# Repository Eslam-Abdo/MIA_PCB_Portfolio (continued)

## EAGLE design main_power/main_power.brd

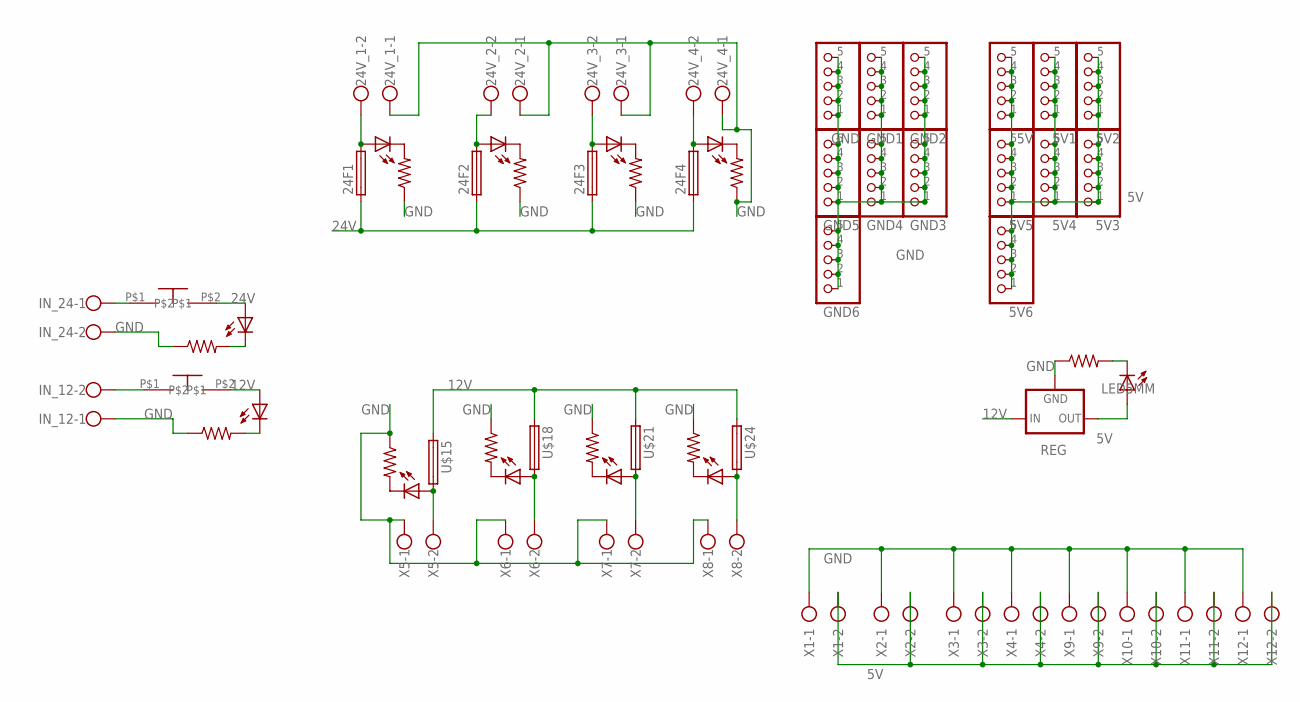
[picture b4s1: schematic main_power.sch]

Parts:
5V, 5V1, 5V2, 5V3, 5V4, 5V5, 5V6: PINHD-1X5; 1X05
12IN: RES-7; 0204/7
12IND: LED5MM
24F1, 24F2, 24F3, 24F4: FUSE_HOLDER; SH22,5A
24V_1, 24V_2, 24V_3, 24V_4: ROSTA.POWER; W239-302
GND, GND1, GND2, GND3, GND4, GND5, GND6: PINHD-1X5; 1X05
IN24: LED5MM
INR24: RES-7; 0204/7
IN_12, IN_24: ROSTA.POWER; W239-302
REG: 78XX-METAL; TO3-79
U$1: 2k; 0204/7
U$2: LED5MM
U$4, U$7, U$10, U$13, U$16, U$19, U$22, U$25: LED3MM
U$5, U$8, U$11, U$14, U$17, U$20, U$23, U$26: RES-7; 0204/7
U$15, U$18, U$21, U$24: FUSE_HOLDER; SH22,5A
U$27, U$28: SWITCH_2; ON_OFF
X1, X2, X3, X4, X9, X10, X11, X12: AK300/22; XTALRR488W60L1090T465H350B
X5, X6, X7, X8: ROSTA.POWER; W239-302

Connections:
5V: 5V.1, 5V.2, 5V.3, 5V.4, 5V.5, 5V1.1, 5V1.2, 5V1.3, 5V1.4, 5V1.5, 5V2.1, 5V2.2, 5V2.3, 5V2.4, 5V2.5, 5V3.1, 5V3.2, 5V3.3, 5V3.4, 5V3.5, 5V4.1, 5V4.2, 5V4.3, 5V4.4, 5V4.5, 5V5.1, 5V5.2, 5V5.3, 5V5.4, 5V5.5, 5V6.1, 5V6.2, 5V6.3, 5V6.4, 5V6.5, REG.1 (OUT), U$2.A, X1.2, X2.2, X3.2, X4.2, X9.2, X10.2, X11.2, X12.2
12V: 12IND.A, REG.3 (IN), U$15.1, U$18.1, U$21.1, U$24.1, U$28.P$2
24V: 24F1.1, 24F2.1, 24F3.1, 24F4.1, IN24.A, U$27.P$2
GND: 12IN.1, 24V_1.1, 24V_2.1, 24V_3.1, 24V_4.1, GND.1, GND.2, GND.3, GND.4, GND.5, GND1.1, GND1.2, GND1.3, GND1.4, GND1.5, GND2.1, GND2.2, GND2.3, GND2.4, GND2.5, GND3.1, GND3.2, GND3.3, GND3.4, GND3.5, GND4.1, GND4.2, GND4.3, GND4.4, GND4.5, GND5.1, GND5.2, GND5.3, GND5.4, GND5.5, GND6.1, GND6.2, GND6.3, GND6.4, GND6.5, INR24.1, IN_12.1, IN_24.2, REG.2 (GND), U$1.1, U$5.1, U$8.1, U$11.1, U$14.1, U$17.1, U$20.1, U$23.1, U$26.1, X1.1, X2.1, X3.1, X4.1, X5.1, X6.1, X7.1, X8.1, X9.1, X10.1, X11.1, X12.1
unnamed: U$1.2, U$2.K (C)
unnamed: 24F1.2, 24V_1.2, U$4.A
unnamed: U$4.K (C), U$5.2
unnamed: IN_12.2, U$28.P$1
unnamed: 24F2.2, 24V_2.2, U$7.A
unnamed: U$7.K (C), U$8.2
unnamed: IN_24.1, U$27.P$1
unnamed: 24F3.2, 24V_3.2, U$10.A
unnamed: U$10.K (C), U$11.2
unnamed: IN24.K (C), INR24.2
unnamed: 24F4.2, 24V_4.2, U$13.A
unnamed: U$13.K (C), U$14.2
unnamed: 12IN.2, 12IND.K (C)
unnamed: U$15.2, U$16.A, X5.2
unnamed: U$16.K (C), U$17.2
unnamed: U$18.2, U$19.A, X6.2
unnamed: U$19.K (C), U$20.2
unnamed: U$21.2, U$22.A, X7.2
unnamed: U$22.K (C), U$23.2
unnamed: U$24.2, U$25.A, X8.2
unnamed: U$25.K (C), U$26.2

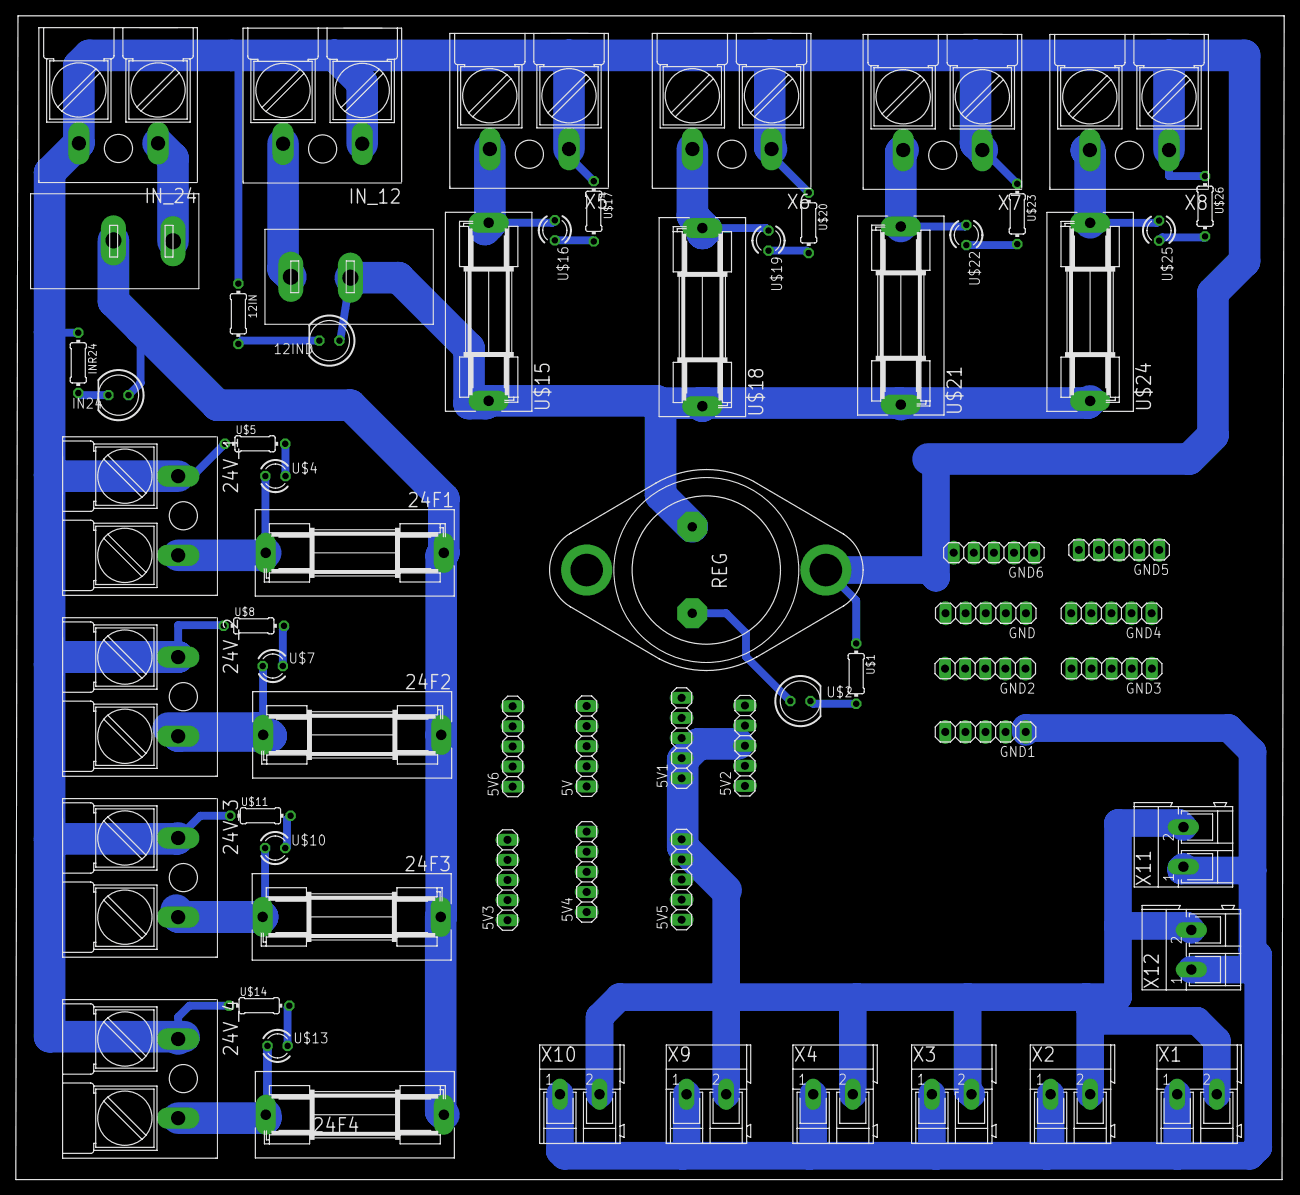
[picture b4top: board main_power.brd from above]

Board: 2 copper layers, 160.3 x 147.1 mm, 65 parts (0 on the bottom side), 25 nets.

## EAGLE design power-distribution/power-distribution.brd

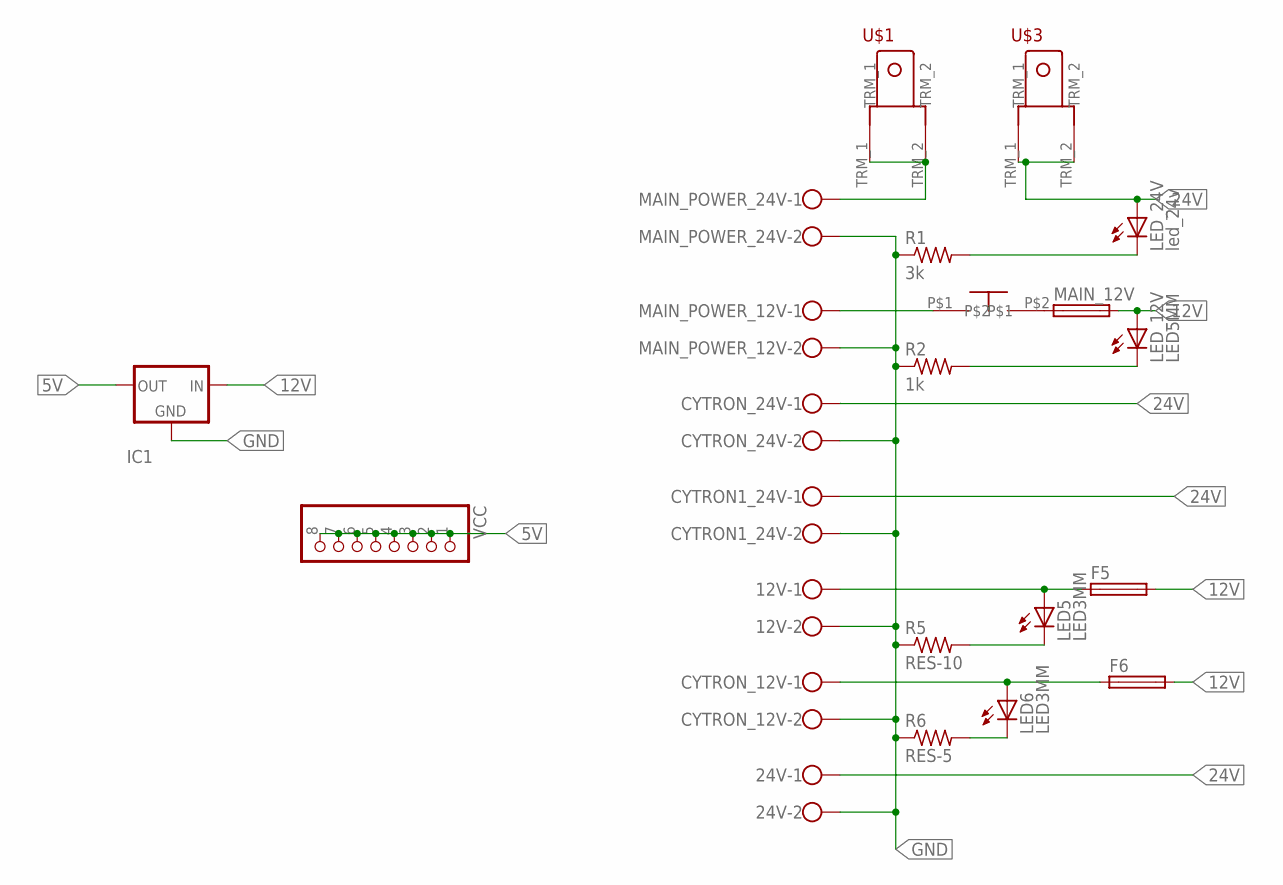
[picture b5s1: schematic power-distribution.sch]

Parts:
12V, 24V: ROSTA.POWER; W239-302
CYTRON1_24V: ROSTA.POWER; W239-302
CYTRON_12V, CYTRON_24V: ROSTA.POWER; W239-302
F5, F6: FUSE_HOLDER; SH22,5A
IC1: 78XX-METAL; TO3-79
LED5, LED6: LED3MM
LED_12V: LED5MM
LED_24V: led_24v; LED5MM
MAIN_12V: FUSE_HOLDER; SH22,5A
MAIN_POWER_12V, MAIN_POWER_24V: ROSTA.POWER; W239-302
R1: 3k; 0204/5
R2: 1k; 0207/12
R5: RES-10; 0207/10
R6: RES-5; 0204/5
U$1, U$3: TERMINAL_EDITED
U$2: SWITCH_2; ON_OFF
VCC: PINHD-1X8; 1X08

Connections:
5V: IC1.1 (OUT), VCC.1, VCC.2, VCC.3, VCC.4, VCC.5, VCC.6, VCC.7, VCC.8
12V: F5.2, F6.2, IC1.3 (IN), LED_12V.A, MAIN_12V.2
24V: 24V.1, CYTRON1_24V.1, CYTRON_24V.1, LED_24V.A, U$3.TRM_1, U$3.TRM_2
GND: 12V.2, 24V.2, CYTRON1_24V.2, CYTRON_12V.2, CYTRON_24V.2, IC1.2 (GND), MAIN_POWER_12V.2, MAIN_POWER_24V.2, R1.1, R2.1, R5.1, R6.1
unnamed: CYTRON_12V.1, F6.1, LED6.A
unnamed: LED_24V.K (C), R1.2
unnamed: MAIN_POWER_24V.1, U$1.TRM_1, U$1.TRM_2
unnamed: LED_12V.K (C), R2.2
unnamed: MAIN_POWER_12V.1, U$2.P$1
unnamed: 12V.1, F5.1, LED5.A
unnamed: LED5.K (C), R5.2
unnamed: MAIN_12V.1, U$2.P$2
unnamed: LED6.K (C), R6.2

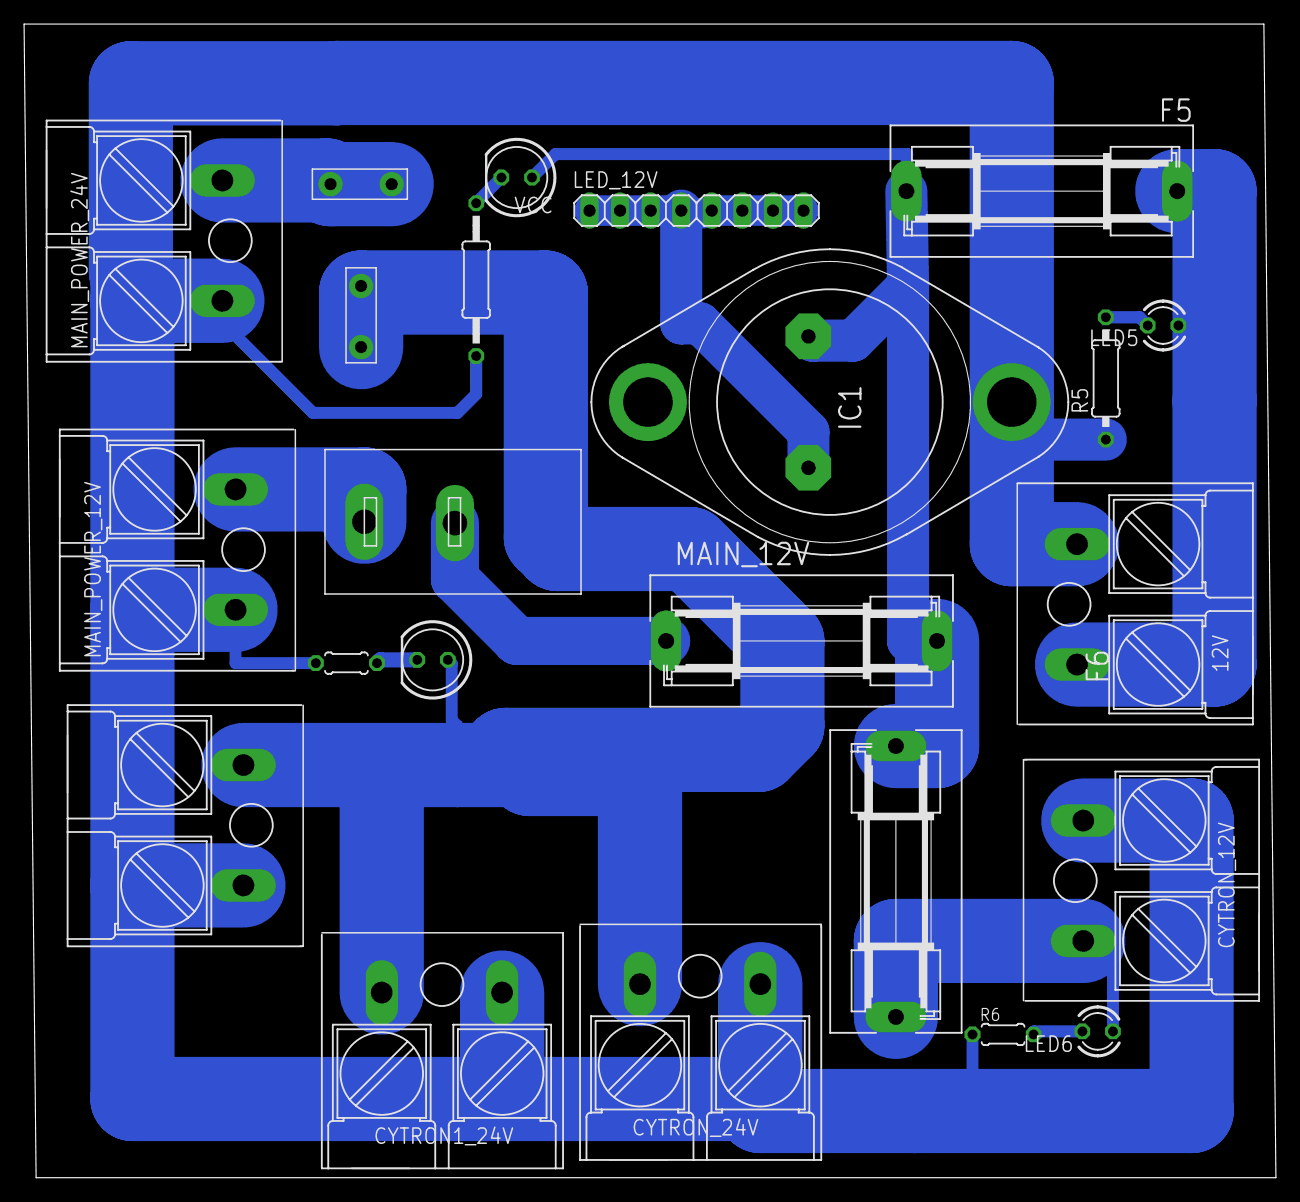
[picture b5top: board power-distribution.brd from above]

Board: 2 copper layers, 104.0 x 95.8 mm, 23 parts (0 on the bottom side), 13 nets.

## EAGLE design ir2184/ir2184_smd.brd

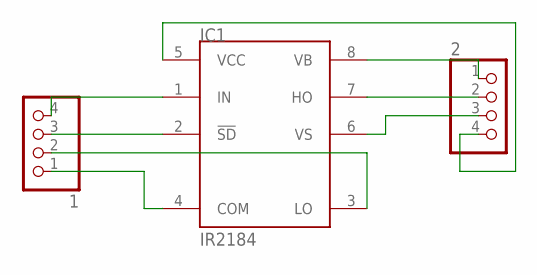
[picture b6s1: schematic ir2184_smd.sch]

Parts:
1, 2: PINHD-1X4; 1X04
IC1: IR2184; SO08

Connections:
COM: 1.1, IC1.4 (COM)
unnamed: 1.4, IC1.1 (IN)
unnamed: 1.3, IC1.2 (!SD)
unnamed: 2.2, IC1.7 (HO)
unnamed: 1.2, IC1.3 (LO)
VB: 2.1, IC1.8 (VB)
VCC: 2.4, IC1.5 (VCC)
VS: 2.3, IC1.6 (VS)

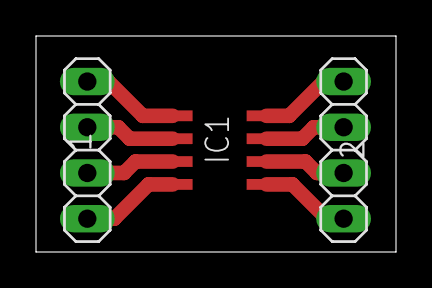
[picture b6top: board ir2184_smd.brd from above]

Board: 2 copper layers, 20.0 x 12.0 mm, 3 parts (0 on the bottom side), 8 nets.

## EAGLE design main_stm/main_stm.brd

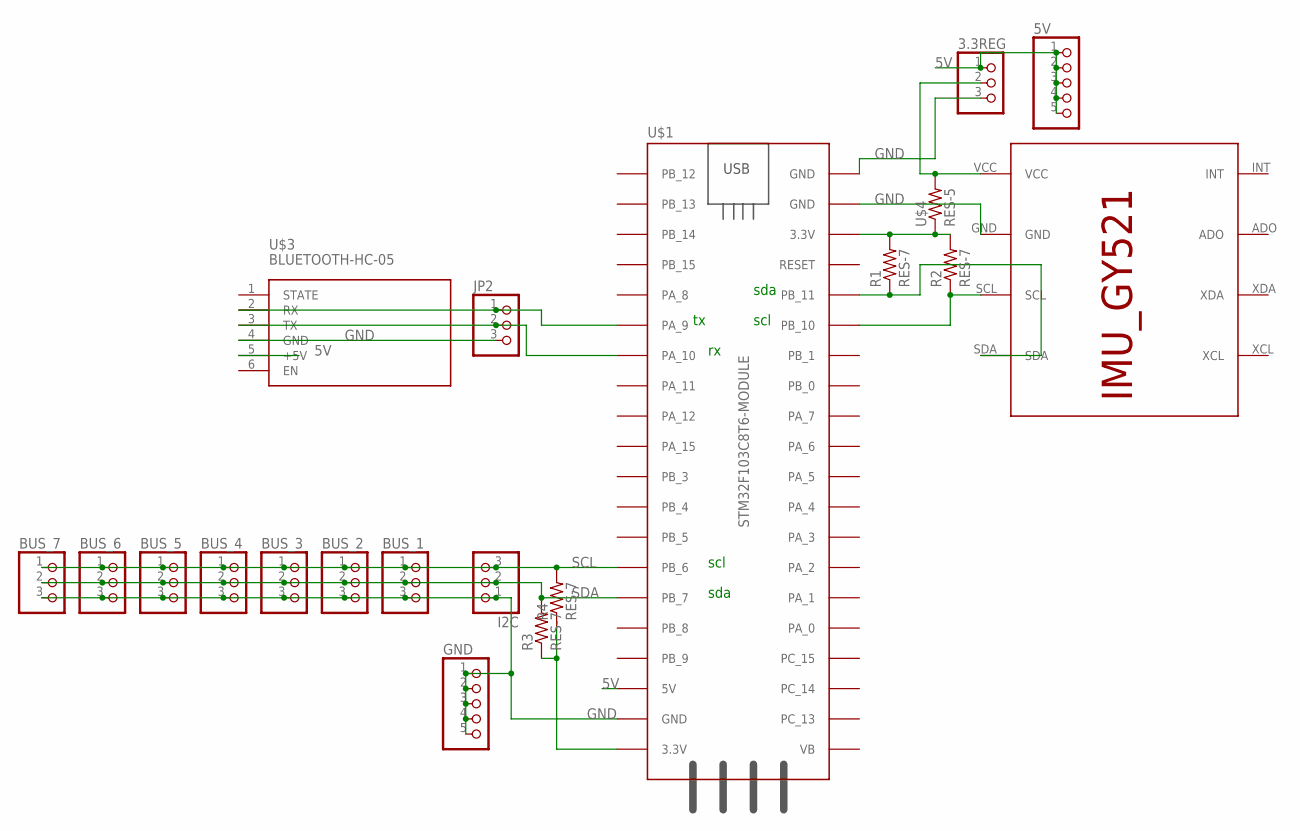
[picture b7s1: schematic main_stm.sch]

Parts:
3.3REG: PINHD-1X3; 1X03
5V: PINHD-1X5; 1X05
BUS_1, BUS_2, BUS_3, BUS_4, BUS_5, BUS_6, BUS_7: PINHD-1X3; 1X03
GND: PINHD-1X5; 1X05
I2C: PINHD-1X3; 1X03
JP2: PINHD-1X3; 1X03
R1, R2, R3, R4: RES-7; 0204/7
U$1: STM32F103C8T6-MODULE
U$2: IMU_ROBOCON_GY521; IMU_GY521
U$3: BLUETOOTH-HC-05; WIRELESS-BLUETOOTH-HC-05
U$4: RES-5; 0204/5

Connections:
5V: 3.3REG.1, 5V.1, 5V.2, 5V.3, 5V.4, 5V.5, U$1.5V, U$3.5 (+5V)
GND: 3.3REG.3, BUS_1.3, BUS_2.3, BUS_3.3, BUS_4.3, BUS_5.3, BUS_6.3, BUS_7.3, GND.1, GND.2, GND.3, GND.4, GND.5, I2C.1, JP2.3, U$1.GND_1 (GND), U$1.GND_2 (GND), U$1.GND_3 (GND), U$2.GND, U$3.4 (GND)
unnamed: R1.1, U$1.PB_11, U$2.SDA
unnamed: R2.1, U$1.PB_10, U$2.SCL
unnamed: R1.2, R2.2, U$1.3.3V_2 (3.3V), U$4.1
unnamed: 3.3REG.2, U$2.VCC, U$4.2
unnamed: R3.1, R4.1, U$1.3.3V_1 (3.3V)
unnamed: JP2.1, U$1.PA_9, U$3.2 (RX)
unnamed: JP2.2, U$1.PA_10, U$3.3 (TX)
SCL: BUS_1.1, BUS_2.1, BUS_3.1, BUS_4.1, BUS_5.1, BUS_6.1, BUS_7.1, I2C.3, R4.2, U$1.PB_6
SDA: BUS_1.2, BUS_2.2, BUS_3.2, BUS_4.2, BUS_5.2, BUS_6.2, BUS_7.2, I2C.2, R3.2, U$1.PB_7

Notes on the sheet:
scl
sda

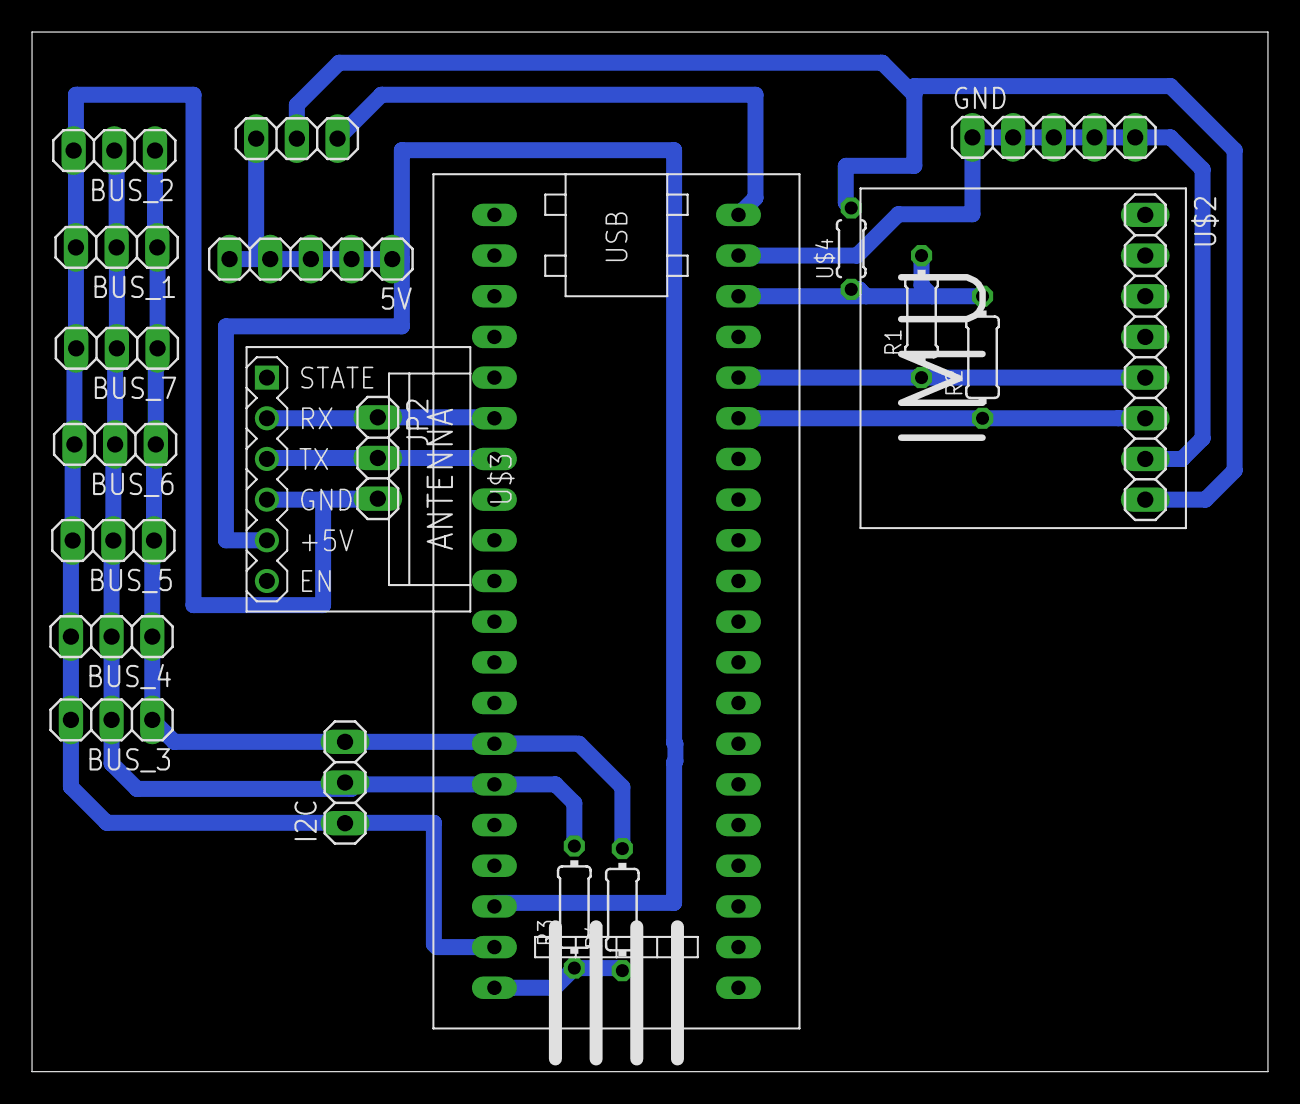
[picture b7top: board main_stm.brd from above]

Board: 2 copper layers, 77.2 x 64.9 mm, 20 parts (0 on the bottom side), 11 nets.

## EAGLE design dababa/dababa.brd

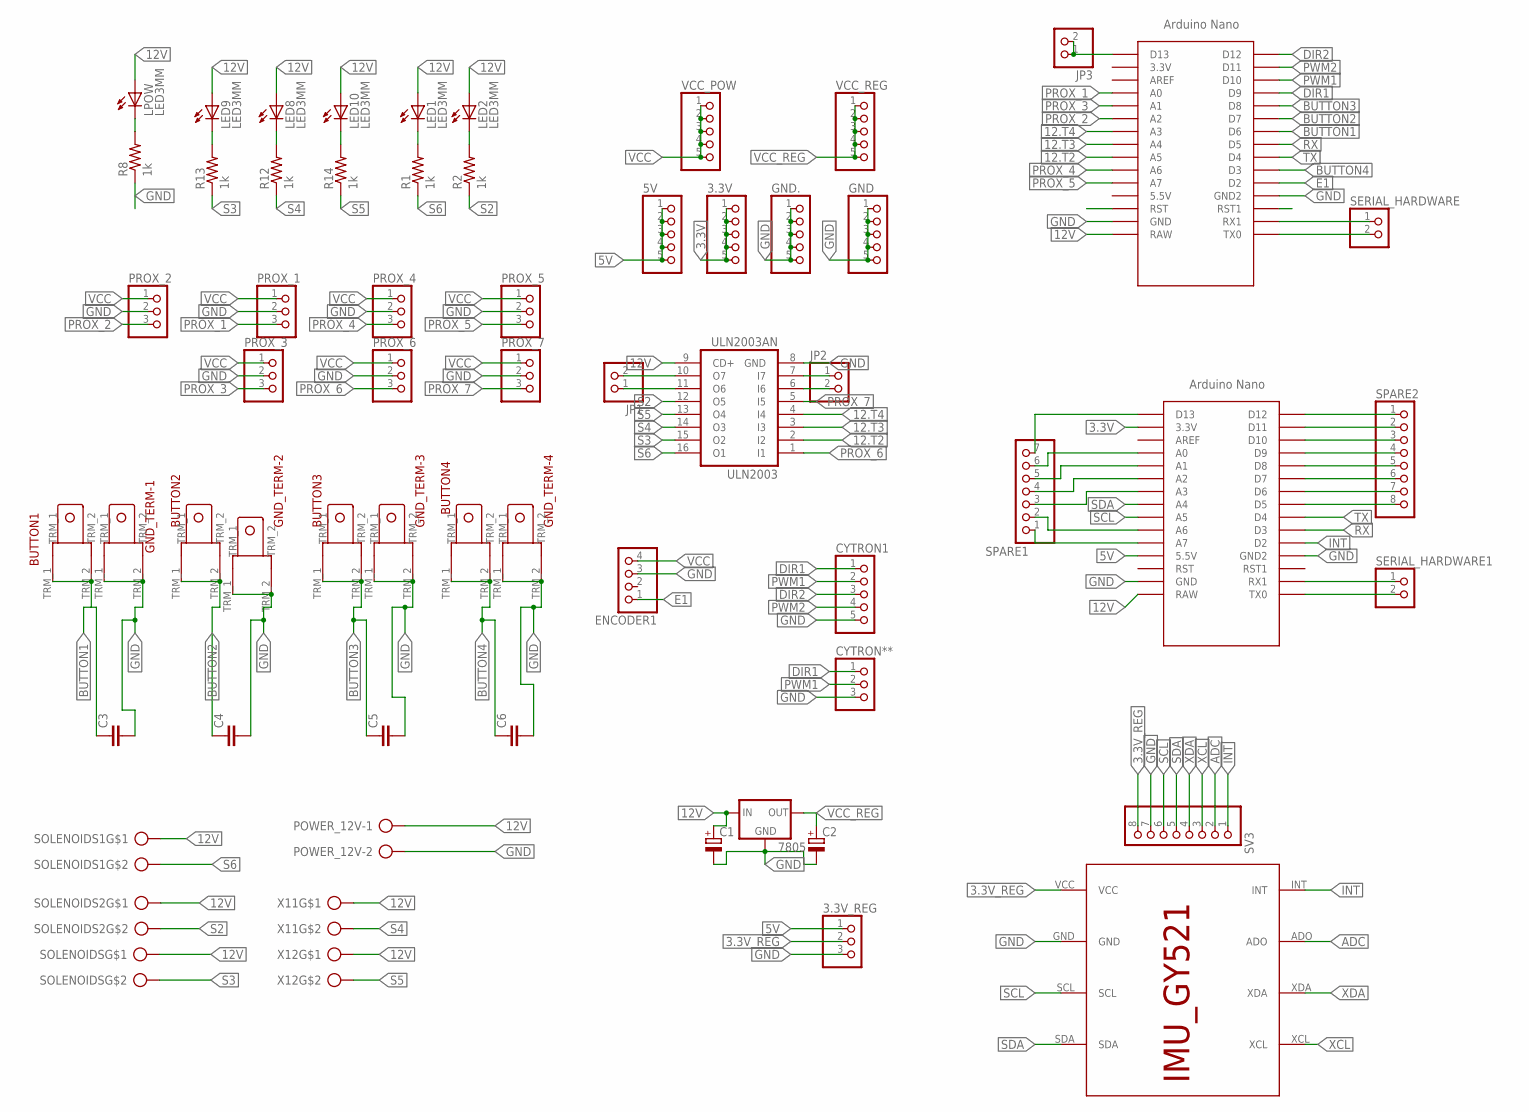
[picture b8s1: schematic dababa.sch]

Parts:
3.3V, 5V: PINHD-1X5; 1X05
3.3V_REG: PINHD-1X3; 1X03
7805: 78XXS
BUTTON1, BUTTON2, BUTTON3, BUTTON4: TERMINAL_EDITED
C1, C2: CAP_POL; E3,5-8
C3, C4, C5, C6: CAPACITOR; C025-025X050
CYTRON1: PINHD-1X5; 1X05
CYTRON**: PINHD-1X3; 1X03
ENCODER1: PINHD-1X4; 1X04
GND, GND.: PINHD-1X5; 1X05
GND_TERM-1, GND_TERM-2, GND_TERM-3, GND_TERM-4: TERMINAL_EDITED
JP1, JP2, JP3: PINHD-1X2; 1X02
LED1, LED2, LED8, LED9, LED10: LED3MM
LPOW: LED3MM
POWER_12V: ROSTA.POWER; W239-302
PROX_1, PROX_2, PROX_3, PROX_4, PROX_5, PROX_6, PROX_7: PINHD-1X3; 1X03
R1, R2, R8, R12, R13, R14: 1k; 0204/5
SERIAL_HARDWARE, SERIAL_HARDWARE1: PINHD-1X2; 1X02
SOLENOIDS, SOLENOIDS1, SOLENOIDS2: CON_PTR_2; AK300/2
SPARE1: PINHD-1X7; 1X07
SPARE2: PINHD-1X8; 1X08
SV3: PINHD-1X8; 1X08
U$1, U$4: ARDUINO_NANO; NANO
U$2: IMU_ROBOCON_GY521; IMU_GY521
ULN2003: ULN2003AN; DIL16
VCC_POW: PINHD-1X5; 1X05
VCC_REG: PINHD-1X5; 1X05
X11, X12: CON_PTR_2; AK300/2

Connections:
3.3V: 3.3V.1, 3.3V.2, 3.3V.3, 3.3V.4, 3.3V.5, U$4.3.3V
3.3V_REG: 3.3V_REG.2, SV3.8, U$2.VCC
5V: 3.3V_REG.1, 5V.1, 5V.2, 5V.3, 5V.4, 5V.5, U$4.5V (5.5V)
12.T2: U$1.A5, ULN2003.2 (I2)
12.T3: U$1.A4, ULN2003.3 (I3)
12.T4: U$1.A3, ULN2003.4 (I4)
12V: 7805.IN, C1.+, LED1.A, LED2.A, LED8.A, LED9.A, LED10.A, LPOW.A, POWER_12V.1, SOLENOIDS.1, SOLENOIDS1.1, SOLENOIDS2.1, U$1.RAW, U$4.RAW, ULN2003.9 (CD+), X11.1, X12.1
ADC: SV3.2, U$2.ADO
BUTTON1: BUTTON1.TRM_1, BUTTON1.TRM_2, C3.1, U$1.D6
BUTTON2: BUTTON2.TRM_1, BUTTON2.TRM_2, C4.1, U$1.D7
BUTTON3: BUTTON3.TRM_1, BUTTON3.TRM_2, C5.1, U$1.D8
BUTTON4: BUTTON4.TRM_1, BUTTON4.TRM_2, C6.1, U$1.D3
DIR1: CYTRON1.1, CYTRON**.1, U$1.D9
DIR2: CYTRON1.3, U$1.D12
E1: ENCODER1.1, U$1.D2
GND: 3.3V_REG.3, 7805.GND, C1.-, C2.-, C3.2, C4.2, C5.2, C6.2, CYTRON1.5, CYTRON**.3, ENCODER1.3, GND.1, GND.2, GND.3, GND.4, GND.5, GND..1, GND..2, GND..3, GND..4, GND..5, GND_TERM-1.TRM_1, GND_TERM-1.TRM_2, GND_TERM-2.TRM_1, GND_TERM-2.TRM_2, GND_TERM-3.TRM_1, GND_TERM-3.TRM_2, GND_TERM-4.TRM_1, GND_TERM-4.TRM_2, POWER_12V.2, PROX_1.2, PROX_2.2, PROX_3.2, PROX_4.2, PROX_5.2, PROX_6.2, PROX_7.2, R8.1, SV3.7, U$1.GND, U$1.GND1 (GND2), U$2.GND, U$4.GND, U$4.GND1 (GND2), ULN2003.8 (GND)
INT: SV3.1, U$2.INT, U$4.D2
unnamed: SERIAL_HARDWARE.1, U$1.RX1
unnamed: SERIAL_HARDWARE.2, U$1.TX0
unnamed: LED1.K (C), R1.2
unnamed: LED2.K (C), R2.2
unnamed: JP1.1, ULN2003.11 (O6)
unnamed: JP1.2, ULN2003.10 (O7)
unnamed: JP2.1, ULN2003.7 (I7)
unnamed: JP2.2, ULN2003.6 (I6)
unnamed: LPOW.K (C), R8.2
unnamed: LED8.K (C), R12.2
unnamed: JP3.1, JP3.2, U$1.D13
unnamed: LED9.K (C), R13.2
unnamed: LED10.K (C), R14.2
unnamed: SERIAL_HARDWARE1.1, U$4.RX1
unnamed: SERIAL_HARDWARE1.2, U$4.TX0
unnamed: SPARE1.3, U$4.A3
unnamed: SPARE1.1, U$4.A7
unnamed: SPARE1.2, U$4.A6
unnamed: SPARE1.4, U$4.A2
unnamed: SPARE1.5, U$4.A1
unnamed: SPARE1.6, U$4.A0
unnamed: SPARE1.7, U$4.D13
unnamed: SPARE2.1, U$4.D12
unnamed: SPARE2.2, U$4.D11
unnamed: SPARE2.3, U$4.D10
unnamed: SPARE2.4, U$4.D9
unnamed: SPARE2.5, U$4.D8
unnamed: SPARE2.6, U$4.D7
unnamed: SPARE2.7, U$4.D6
unnamed: SPARE2.8, U$4.D5
PROX_1: PROX_1.3, U$1.A0
PROX_2: PROX_2.3, U$1.A2
PROX_3: PROX_3.3, U$1.A1
PROX_4: PROX_4.3, U$1.A6
PROX_5: PROX_5.3, U$1.A7
PROX_6: PROX_6.3, ULN2003.1 (I1)
PROX_7: PROX_7.3, ULN2003.5 (I5)
PWM1: CYTRON1.2, CYTRON**.2, U$1.D10
PWM2: CYTRON1.4, U$1.D11
RX: U$1.D5, U$4.D3
S2: R2.1, SOLENOIDS2.2, ULN2003.12 (O5)
S3: R13.1, SOLENOIDS.2, ULN2003.15 (O2)
S4: R12.1, ULN2003.14 (O3), X11.2
S5: R14.1, ULN2003.13 (O4), X12.2
S6: R1.1, SOLENOIDS1.2, ULN2003.16 (O1)
SCL: SV3.6, U$2.SCL, U$4.A5
SDA: SV3.5, U$2.SDA, U$4.A4
TX: U$1.D4, U$4.D4
VCC: ENCODER1.4, PROX_1.1, PROX_2.1, PROX_3.1, PROX_4.1, PROX_5.1, PROX_6.1, PROX_7.1, VCC_POW.1, VCC_POW.2, VCC_POW.3, VCC_POW.4, VCC_POW.5
VCC_REG: 7805.OUT, C2.+, VCC_REG.1, VCC_REG.2, VCC_REG.3, VCC_REG.4, VCC_REG.5
XCL: SV3.3, U$2.XCL
XDA: SV3.4, U$2.XDA

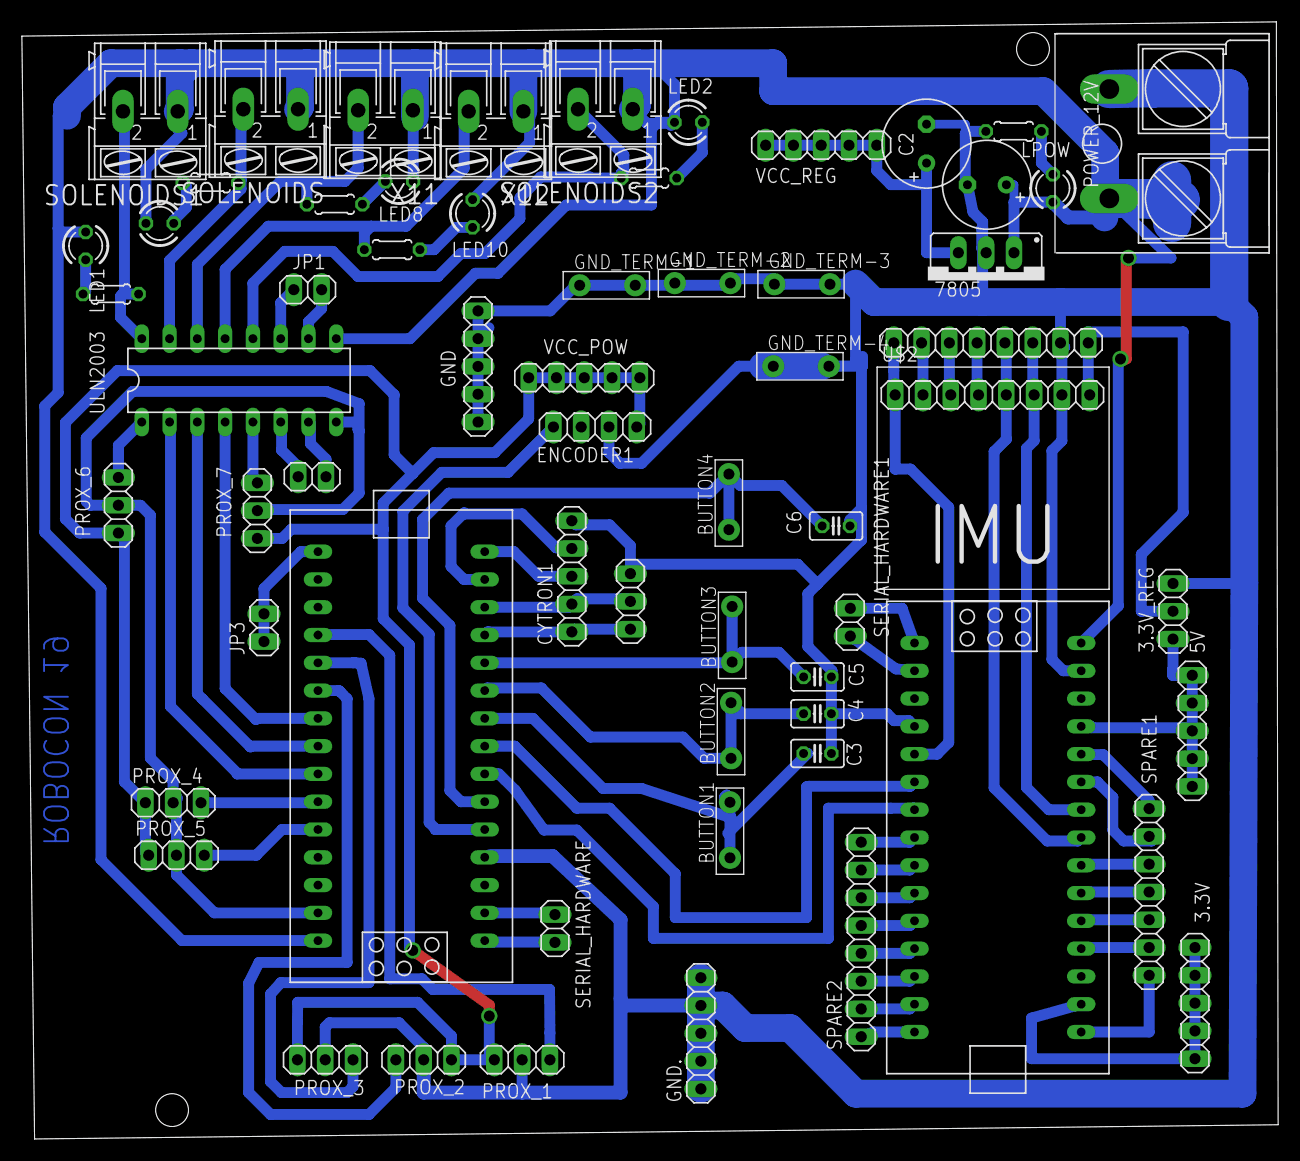
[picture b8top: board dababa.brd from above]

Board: 2 copper layers, 114.8 x 102.1 mm, 62 parts (0 on the bottom side), 69 nets.

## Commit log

2023-04-14 add files
2023-04-15 readme
2023-04-15 change width of pics
2023-04-15 update motor driver
2023-04-15 change name of dir
2023-04-15 dir name changed
2023-04-15 add base versions
2023-04-15 add pics
2023-04-15 update readme file
2023-04-15 update pic
